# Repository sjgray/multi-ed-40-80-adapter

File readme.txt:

PET/CBM Multi-EditROM with 40/80 column switcher Adapter
========================================================

This adapter lets your PET/CBM computer with Universal Dynamic PET motherboard
to have up to 16 Edit ROM available and selectable via DIP Switch or Toggle Switch.
and adds the ability for the video to be switched between 40 or 80 columns either
via software, or toggle switch (selectable).

Use my Multi-EDIT-ROM-Builder program (also available on github) to combine
up to 16 editor roms into a single 64K EPROM.

Use my PET/CBM EditROM Project to create custom Editor ROMs with various features
including software-switchable 40/80 column support via this board.

More information and assembly instructions at:
http://www.cbmsteve.ca
http://www.cbmsteve.ca/multied4080/index.html

Steve

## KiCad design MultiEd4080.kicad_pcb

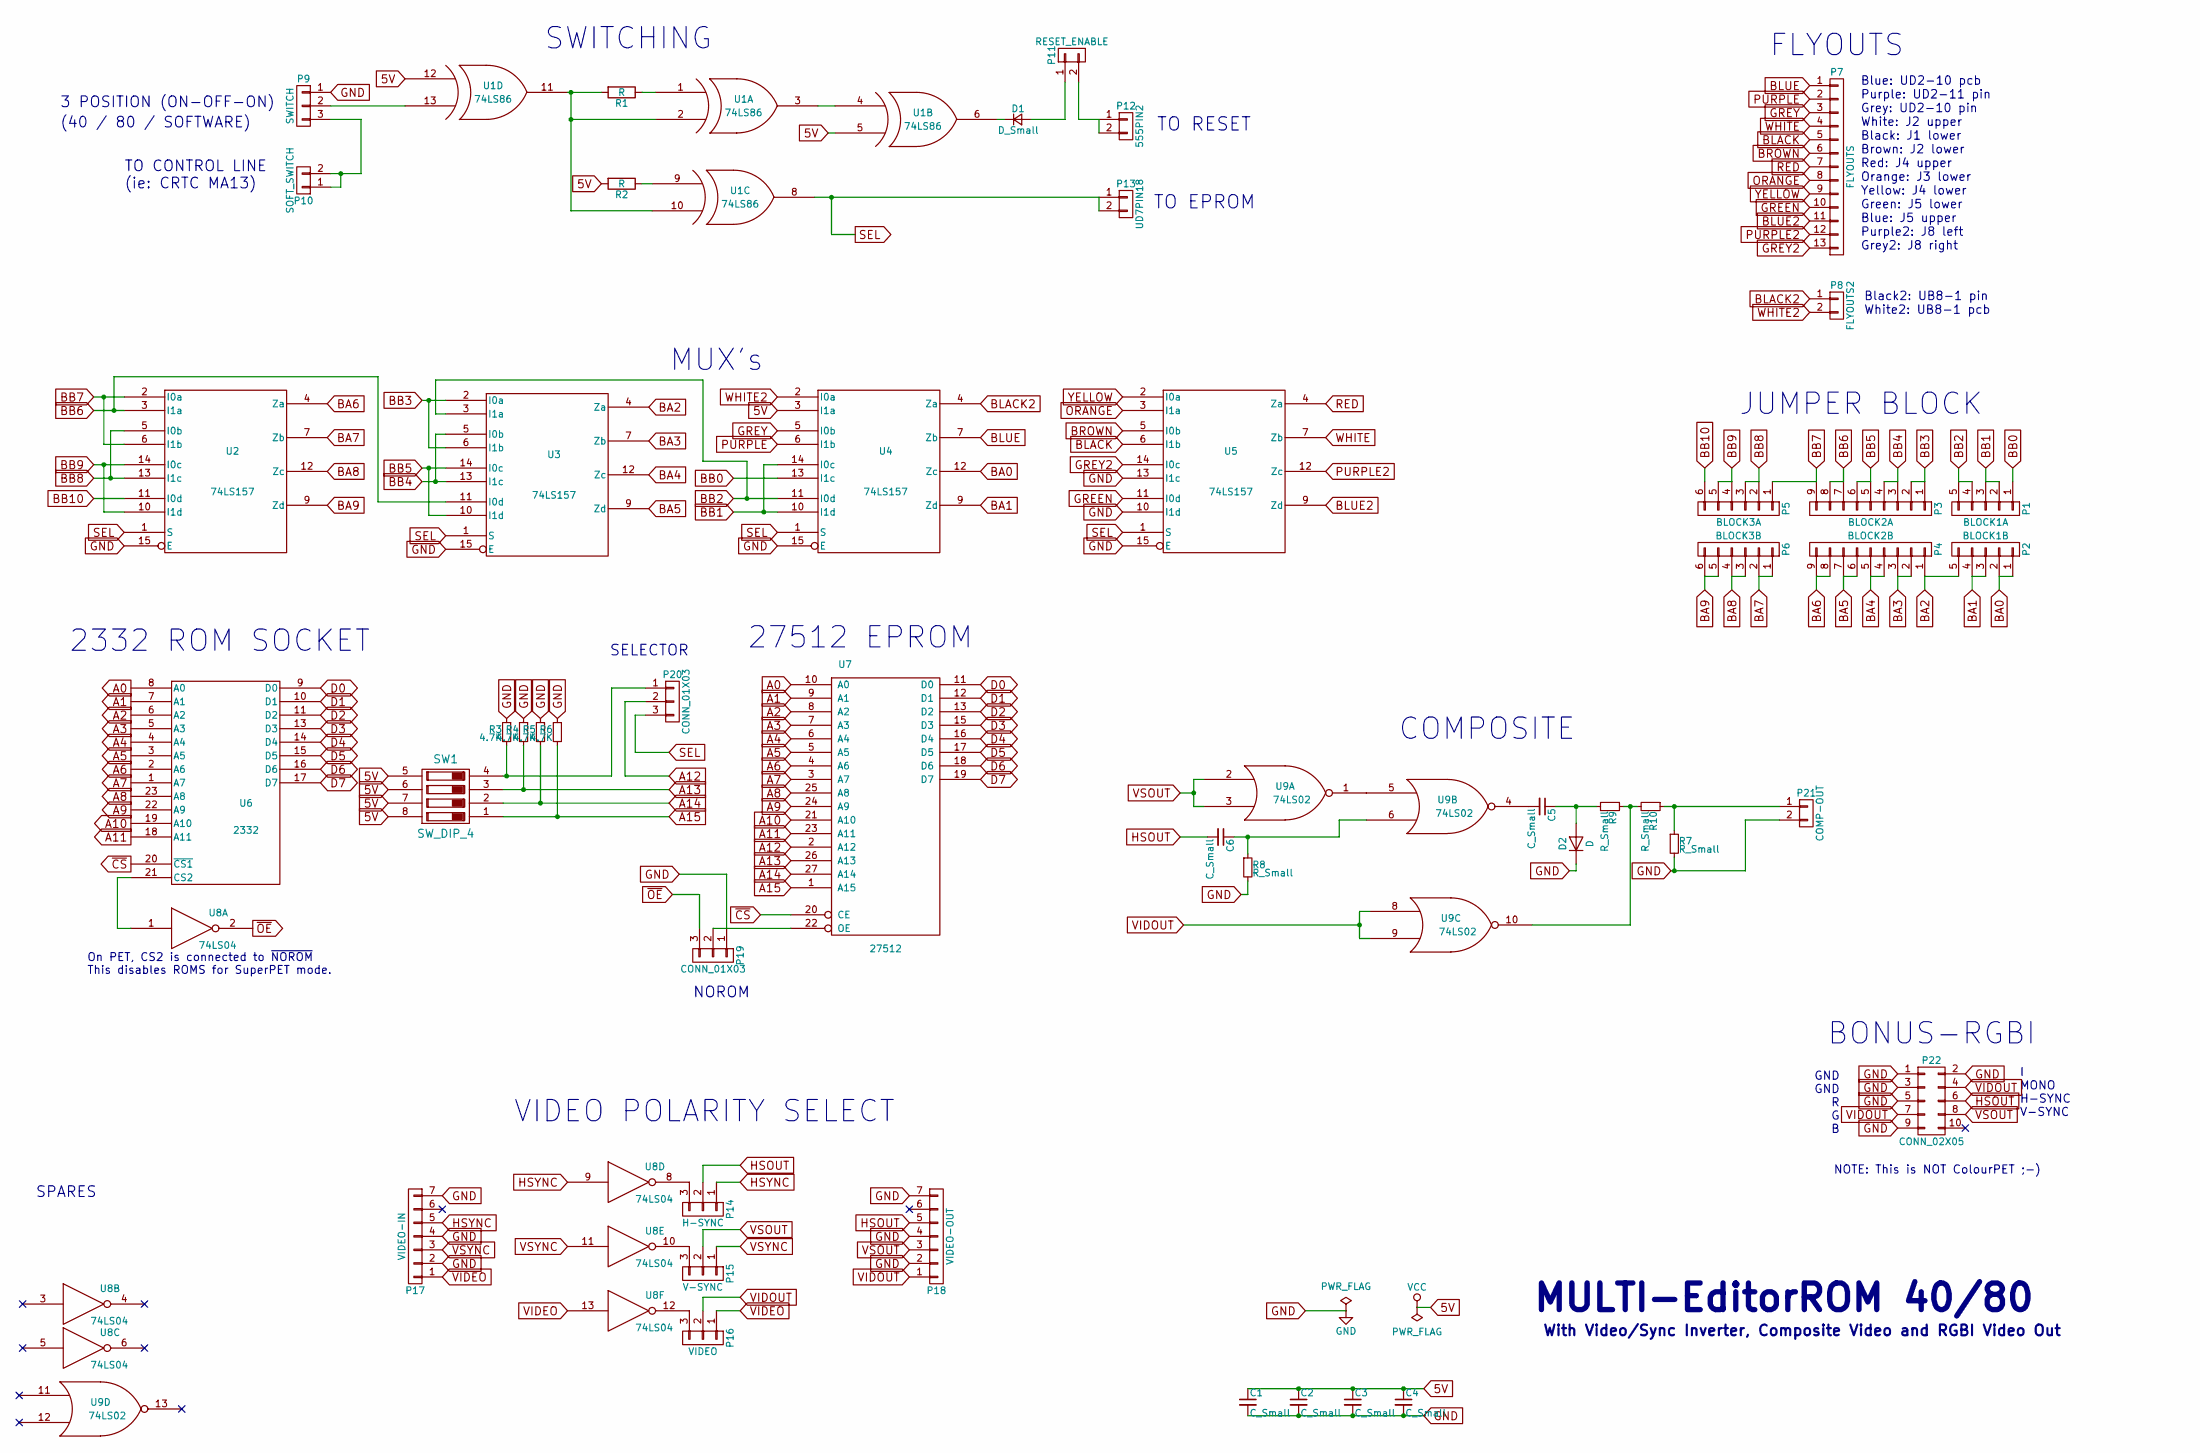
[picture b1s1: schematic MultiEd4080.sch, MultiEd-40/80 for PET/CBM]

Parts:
C1, C2, C3, C4, C5, C6: C_Small; C_Disc_D3.8mm_W2.6mm_P2.50mm
D1: D_Small; D_DO-41_SOD81_P7.62mm_Horizontal
D2: D; D_DO-41_SOD81_P7.62mm_Horizontal
P1: BLOCK1A; Pin_Header_Straight_1x05_Pitch2.54mm
P2: BLOCK1B; Pin_Header_Straight_1x05_Pitch2.54mm
P3: BLOCK2A; Pin_Header_Straight_1x09_Pitch2.54mm
P4: BLOCK2B; Pin_Header_Straight_1x09_Pitch2.54mm
P5: BLOCK3A; Pin_Header_Straight_1x06_Pitch2.54mm
P6: BLOCK3B; Pin_Header_Straight_1x06_Pitch2.54mm
P7: FLYOUTS; Pin_Header_Straight_1x13_Pitch2.54mm
P8: FLYOUTS2; Pin_Header_Straight_1x02_Pitch2.54mm
P9: SWITCH; Pin_Header_Straight_1x03_Pitch2.54mm
P10: SOFT_SWITCH; Pin_Header_Straight_1x02_Pitch2.54mm
P11: RESET_ENABLE; Pin_Header_Straight_1x02_Pitch2.54mm
P12: 555PIN2; Pin_Header_Straight_1x02_Pitch2.54mm
P13: UD7PIN18; Pin_Header_Straight_1x02_Pitch2.54mm
P14: H-SYNC; Pin_Header_Straight_1x03_Pitch2.54mm
P15: V-SYNC; Pin_Header_Straight_1x03_Pitch2.54mm
P16: VIDEO; Pin_Header_Straight_1x03_Pitch2.54mm
P17: VIDEO-IN; Pin_Header_Straight_1x07_Pitch2.54mm
P18: VIDEO-OUT; Pin_Header_Straight_1x07_Pitch2.54mm
P19, P20: CONN_01X03; Pin_Header_Straight_1x03_Pitch2.54mm
P21: COMP-OUT; Pin_Header_Straight_1x02_Pitch2.54mm
P22: CONN_02X05; Pin_Header_Straight_2x05_Pitch2.54mm
R1, R2: R; R_Axial_DIN0204_L3.6mm_D1.6mm_P5.08mm_Horizontal
R3, R4, R5, R6: 4.7K; R_Axial_DIN0204_L3.6mm_D1.6mm_P5.08mm_Horizontal
R7, R8, R9, R10: R_Small; R_Axial_DIN0204_L3.6mm_D1.6mm_P5.08mm_Horizontal
SW1: SW_DIP_4; DIP-8_W7.62mm_LongPads
U1: 74LS86; DIP-14_W7.62mm_LongPads
U2, U3, U4, U5: 74LS157; DIP-16_W7.62mm_LongPads
U6: 2332; DIP-24_W15.24mm_LongPads
U7: 27512; DIP-28_W15.24mm_LongPads
U8: 74LS04; DIP-14_W7.62mm_LongPads
U9: 74LS02; DIP-14_W7.62mm_LongPads

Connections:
5V: C1.1, C2.1, C3.1, C4.1, R2.2, SW1.5, SW1.6, SW1.7, SW1.8, U1.5 (IN2), U1.12 (IN1), U1.14 (VCC), U2.16 (VCC), U3.16 (VCC), U4.3 (I1a), U4.16 (VCC), U5.16 (VCC), U6.24 (Vcc), U7.28 (VCC), U8.14 (VCC), U9.14 (VCC)
A0: U6.8 (A0), U7.10 (A0)
A1: U6.7 (A1), U7.9 (A1)
A2: U6.6 (A2), U7.8 (A2)
A3: U6.5 (A3), U7.7 (A3)
A4: U6.4 (A4), U7.6 (A4)
A5: U6.3 (A5), U7.5 (A5)
A6: U6.2 (A6), U7.4 (A6)
A7: U6.1 (A7), U7.3 (A7)
A8: U6.23 (A8), U7.25 (A8)
A9: U6.22 (A9), U7.24 (A9)
A10: U6.19 (A10), U7.21 (A10)
A11: U6.18 (A11), U7.23 (A11)
A12: P20.2, U7.2 (A12)
A13: R4.2, SW1.3, U7.26 (A13)
A14: R5.2, SW1.2, U7.27 (A14)
A15: R6.2, SW1.1, U7.1 (A15)
BA0: P2.1, P2.2, U4.12 (Zc)
BA1: P2.3, P2.4, U4.9 (Zd)
BA2: P2.5, P4.1, U3.4 (Za)
BA3: P4.2, P4.3, U3.7 (Zb)
BA4: P4.4, P4.5, U3.12 (Zc)
BA5: P4.6, P4.7, U3.9 (Zd)
BA6: P4.8, P4.9, U2.4 (Za)
BA7: P6.1, P6.2, U2.7 (Zb)
BA8: P6.3, P6.4, U2.12 (Zc)
BA9: P6.5, P6.6, U2.9 (Zd)
BB0: P1.1, U4.13 (I1c)
BB1: P1.2, P1.3, U4.10 (I1d), U4.14 (I0c)
BB2: P1.4, P1.5, U3.3 (I1a), U4.11 (I0d)
BB3: P3.1, P3.2, U3.2 (I0a), U3.6 (I1b)
BB4: P3.3, P3.4, U3.5 (I0b), U3.13 (I1c)
BB5: P3.5, P3.6, U3.10 (I1d), U3.14 (I0c)
BB6: P3.7, P3.8, U2.3 (I1a), U3.11 (I0d)
BB7: P3.9, P5.1, U2.2 (I0a), U2.6 (I1b)
BB8: P5.2, P5.3, U2.5 (I0b), U2.13 (I1c)
BB9: P5.4, P5.5, U2.10 (I1d), U2.14 (I0c)
BB10: P5.6, U2.11 (I0d)
BLACK: P7.5, U5.6 (I1b)
BLACK2: P8.1, U4.4 (Za)
BLUE: P7.1, U4.7 (Zb)
BLUE2: P7.11, U5.9 (Zd)
BROWN: P7.6, U5.5 (I0b)
D0: U6.9 (D0), U7.11 (D0)
D1: U6.10 (D1), U7.12 (D1)
D2: U6.11 (D2), U7.13 (D2)
D3: U6.13 (D3), U7.15 (D3)
D4: U6.14 (D4), U7.16 (D4)
D5: U6.15 (D5), U7.17 (D5)
D6: U6.16 (D6), U7.18 (D6)
D7: U6.17 (D7), U7.19 (D7)
GND: C1.2, C2.2, C3.2, C4.2, D2.1 (K), P9.1, P17.2, P17.4, P17.7, P18.2, P18.4, P18.7, P19.1, P21.2, P22.1, P22.2, P22.3, P22.5, P22.9, R3.1, R4.1, R5.1, R6.1, R7.2, R8.2, U1.7 (GND), U2.8 (GND), U2.15 (E), U3.8 (GND), U3.15 (E), U4.8 (GND), U4.15 (E), U5.8 (GND), U5.10 (I1d), U5.13 (I1c), U5.15 (E), U6.12 (GND), U7.14 (GND), U8.7 (GND), U9.7 (GND)
GREEN: P7.10, U5.11 (I0d)
GREY: P7.3, U4.5 (I0b)
GREY2: P7.13, U5.14 (I0c)
HSOUT: C6.2, P14.2, P18.5, P22.6
HSYNC: P14.1, P17.5, U8.9
unnamed: C5.1, D2.2 (A), R9.2
unnamed: C5.2, U9.4
unnamed: C6.1, R8.1, U9.6
unnamed: D1.1 (K), U1.6 (OUT)
unnamed: D1.2 (A), P11.1
unnamed: P9.2, U1.13 (IN2)
unnamed: P9.3, P10.1, P10.2
unnamed: P11.2, P12.1, P12.2
unnamed: P14.3, U8.8
unnamed: P15.3, U8.10
unnamed: P16.3, U8.12
unnamed: P19.2, U7.22 (OE)
unnamed: P20.1, R3.2, SW1.4
unnamed: P21.1, R7.1, R10.1
unnamed: R1.1, U1.1 (IN1)
unnamed: R1.2, U1.2 (IN2), U1.10 (IN2), U1.11 (OUT)
unnamed: R2.1, U1.9 (IN1)
unnamed: R9.1, R10.2, U9.10
unnamed: U1.3 (OUT), U1.4 (IN1)
unnamed: U6.21 (CS2), U8.1
unnamed: U9.1, U9.5
ORANGE: P7.8, U5.3 (I1a)
PURPLE: P7.2, U4.6 (I1b)
PURPLE2: P7.12, U5.12 (Zc)
RED: P7.7, U5.4 (Za)
SEL: P13.1, P13.2, P20.3, U1.8 (OUT), U2.1 (S), U3.1 (S), U4.1 (S), U5.1 (S)
VIDEO: P16.1, P17.1, U8.13
VIDOUT: P16.2, P18.1, P22.4, P22.7, U9.8, U9.9
VSOUT: P15.2, P18.3, P22.8, U9.2, U9.3
VSYNC: P15.1, P17.3, U8.11
WHITE: P7.4, U5.7 (Zb)
WHITE2: P8.2, U4.2 (I0a)
YELLOW: P7.9, U5.2 (I0a)
~CS: U6.20 (~CS1), U7.20 (CE)
~OE: P19.3, U8.2

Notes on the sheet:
With Video/Sync Inverter, Composite Video and RGBI Video Out
SWITCHING
FLYOUTS
TO EPROM
TO RESET
JUMPER BLOCK
MUX's
Blue: UD2-10 pcb Purple: UD2-11 pin Grey: UD2-10 pin White: J2 upper Black: J1 lower Brown: J2 lower Red: J4 upper Orange: J3 lower Yellow: J4 lower Green: J5 lower Blue: J5 upper Purple2: J8 left Grey2: J8 right
Black2: UB8-1 pin White2: UB8-1 pcb
2332 ROM SOCKET
27512 EPROM
SELECTOR
MULTI-EditorROM 40/80
On PET, CS2 is connected to ~NOROM~ This disables ROMS for SuperPET mode.
SPARES
VIDEO POLARITY SELECT
3 POSITION (ON-OFF-ON)
TO CONTROL LINE (ie: CRTC MA13)
(40 / 80 / SOFTWARE)
COMPOSITE
BONUS-RGBI
GND GND R G B
I MONO H-SYNC V-SYNC
NOTE: This is NOT ColourPET ;-)
NOROM

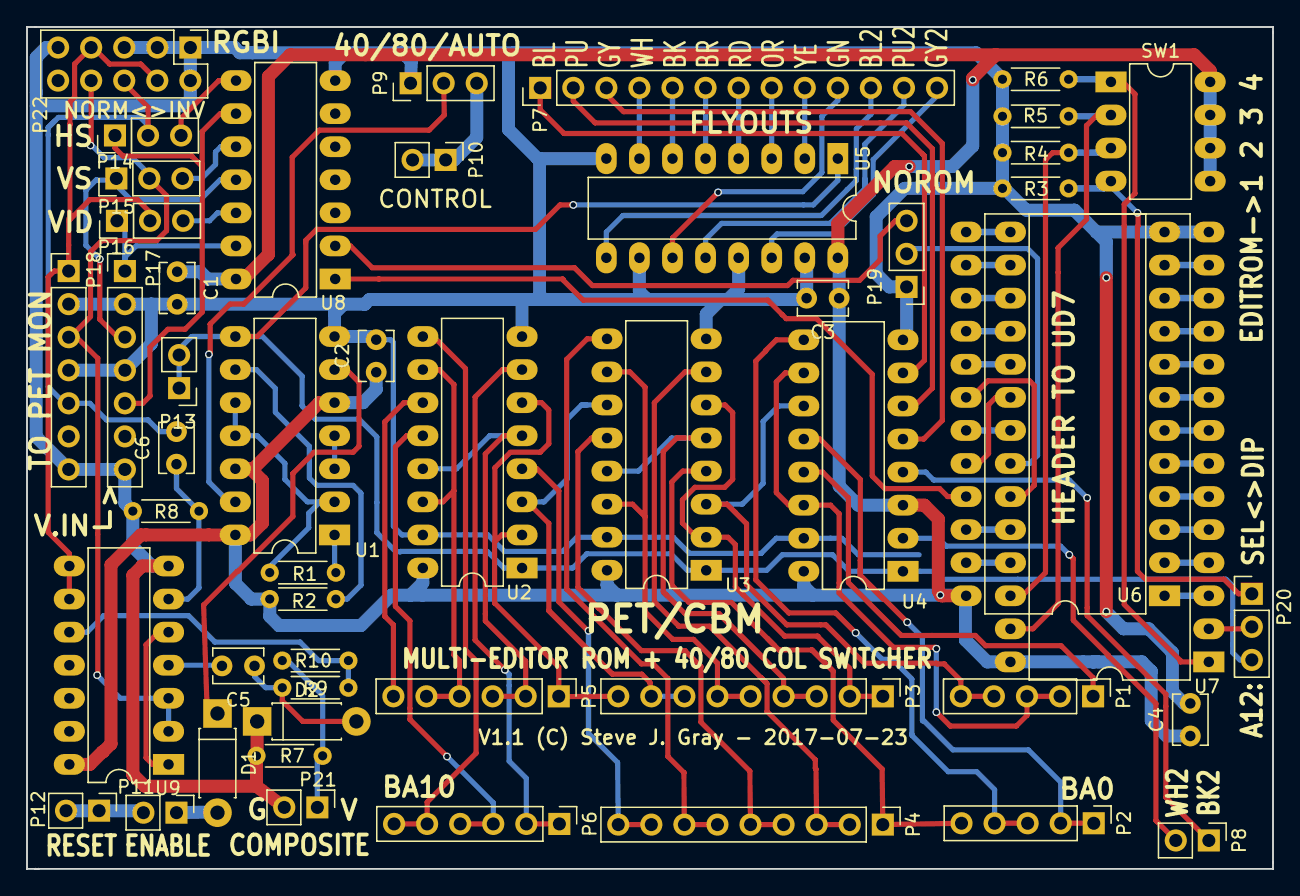
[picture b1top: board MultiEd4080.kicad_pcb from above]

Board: 2 copper layers, 95.7 x 64.7 mm, 50 parts (0 on the bottom side), 92 nets.

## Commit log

2021-08-06 :confetti_ball: Added .gitattributes & .gitignore files
2021-08-06 Initial commit
    Multi-EditROM with 40/80 column switching..
2025-01-15 Update webpage
    http://www.cbmsteve.ca/
